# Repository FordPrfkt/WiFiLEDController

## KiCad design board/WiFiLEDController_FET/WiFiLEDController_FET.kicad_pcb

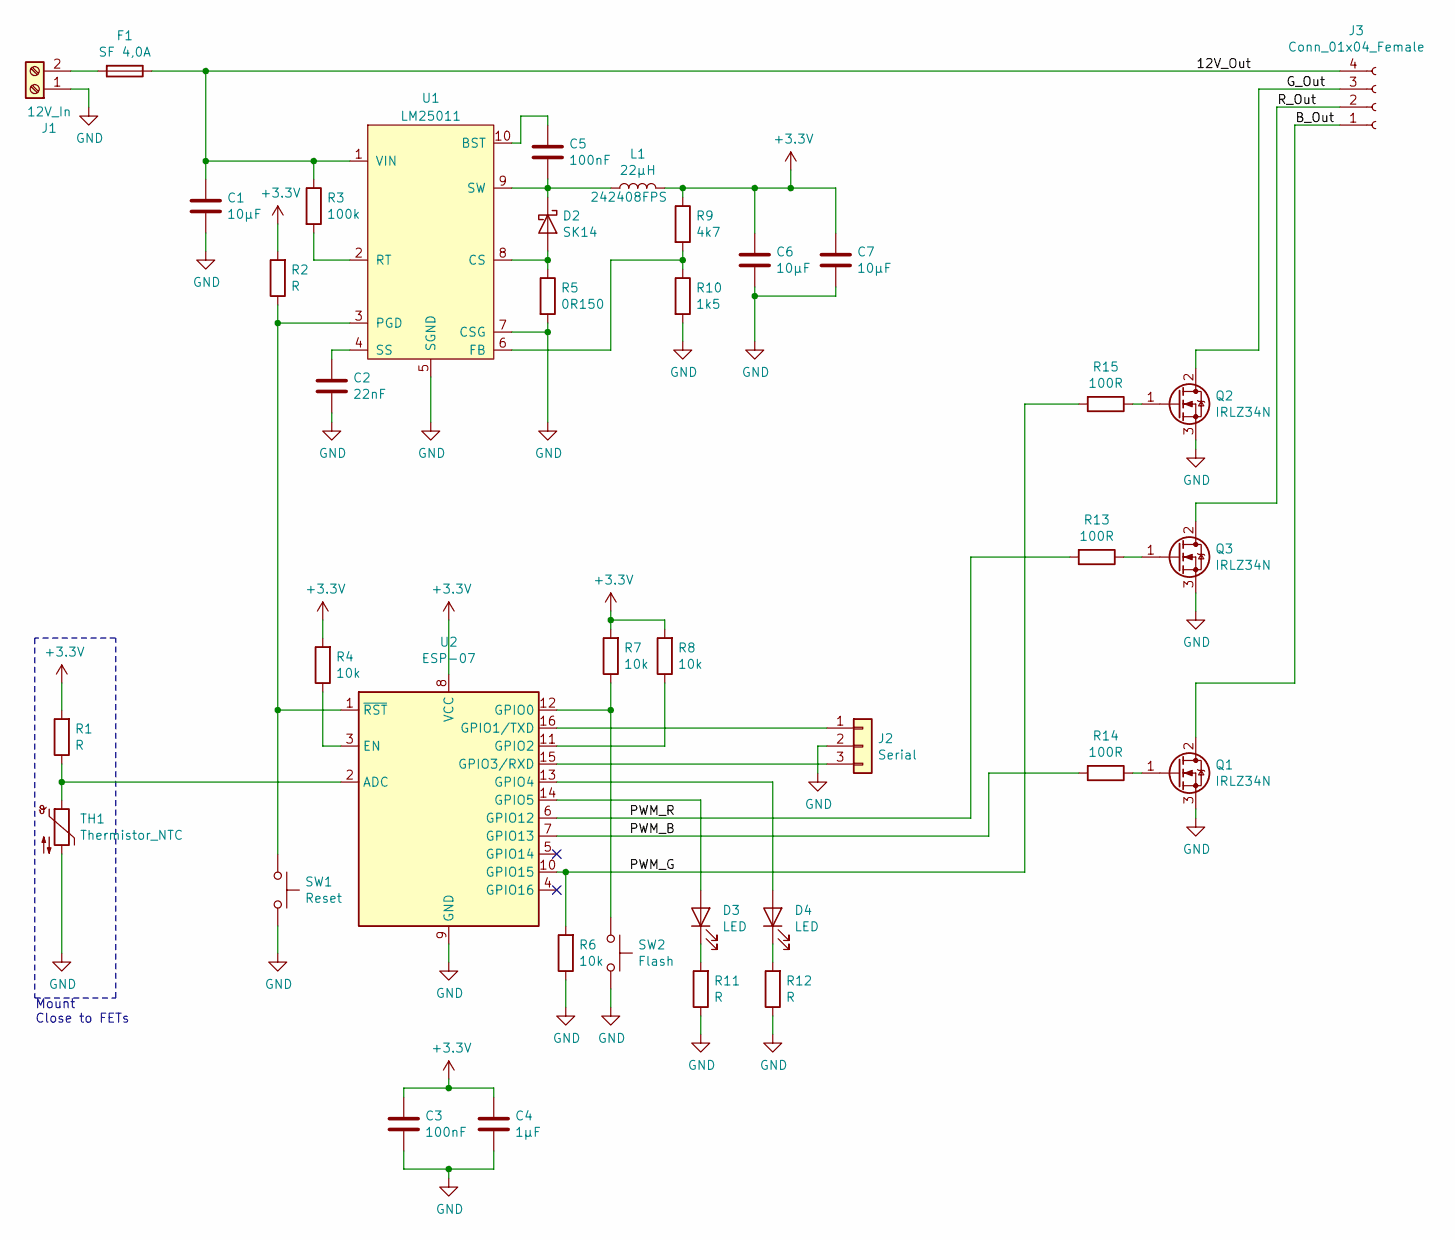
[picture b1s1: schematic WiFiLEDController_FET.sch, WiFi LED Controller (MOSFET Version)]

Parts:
C1: 10µF; C_1210_3225Metric_Pad1.42x2.65mm_HandSolder
C2: 22nF; C_0805_2012Metric_Pad1.15x1.40mm_HandSolder
C3, C5: 100nF; C_0805_2012Metric_Pad1.15x1.40mm_HandSolder
C4: 1µF; C_0805_2012Metric_Pad1.15x1.40mm_HandSolder
C6, C7: 10µF; C_1206_3216Metric_Pad1.42x1.75mm_HandSolder
D2: SK14; D_SOD-123
D3, D4: LED; LED_0805_2012Metric_Pad1.15x1.40mm_HandSolder
F1: SF 4,0A; R_Axial_DIN0207_L6.3mm_D2.5mm_P10.16mm_Horizontal
J1: 12V_In; TerminalBlock_RND_205-00001_1x02_P5.00mm_Horizontal
J2: Serial; PinHeader_1x03_P2.54mm_Vertical
J3: Conn_01x04_Female; PinSocket_1x04_P2.54mm_Horizontal
L1: 22µH; L_6.3x6.3_H3
Q1, Q2, Q3: IRLZ34N; TO-220-3_Horizontal_TabDown
R1, R2, R11, R12: R; R_0805_2012Metric_Pad1.15x1.40mm_HandSolder
R3: 100k; R_0805_2012Metric_Pad1.15x1.40mm_HandSolder
R4, R6, R7, R8: 10k; R_0805_2012Metric_Pad1.15x1.40mm_HandSolder
R5: 0R150; R_0805_2012Metric_Pad1.15x1.40mm_HandSolder
R9: 4k7; R_0805_2012Metric_Pad1.15x1.40mm_HandSolder
R10: 1k5; R_0805_2012Metric_Pad1.15x1.40mm_HandSolder
R13, R14, R15: 100R; R_0805_2012Metric_Pad1.15x1.40mm_HandSolder
SW1: Reset; SW_SPST_B3S-1000
SW2: Flash; SW_SPST_B3S-1000
TH1: Thermistor_NTC; R_0805_2012Metric_Pad1.15x1.40mm_HandSolder
U1: LM25011; HVSSOP-10
U2: ESP-07

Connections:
+3V3: C3.1, C4.1, C6.1, C7.1, L1.2, R1.2, R2.2, R4.2, R7.2, R8.2, R9.1, U2.8 (VCC)
/12V_Out: C1.1, F1.1, J3.4, R3.1, U1.1 (VIN)
/B_Out: J3.1, Q1.2 (D)
/G_Out: J3.3, Q2.2 (D)
/PWM_B: R14.2, U2.7 (GPIO13)
/PWM_G: R6.2, R15.2, U2.10 (GPIO15)
/PWM_R: R13.2, U2.6 (GPIO12)
/R_Out: J3.2, Q3.2 (D)
GND: C1.2, C2.2, C3.2, C4.2, C6.2, C7.2, J1.1, J2.2, Q1.3 (S), Q2.3 (S), Q3.3 (S), R5.2, R6.1, R10.2, R11.1, R12.1, SW1.2, SW2.2, TH1.2, U1.5 (SGND), U1.7 (CSG), U1.11 (GND), U2.9 (GND)
unnamed: C2.1, U1.4 (SS)
unnamed: C5.1, U1.10 (BST)
unnamed: C5.2, D2.1 (K), L1.1, U1.9 (SW)
unnamed: D2.2 (A), R5.1, U1.8 (CS)
unnamed: D3.1 (K), R11.2
unnamed: D3.2 (A), U2.14 (GPIO5)
unnamed: D4.1 (K), R12.2
unnamed: D4.2 (A), U2.13 (GPIO4)
unnamed: F1.2, J1.2
unnamed: J2.1, U2.16 (GPIO1/TXD)
unnamed: J2.3, U2.15 (GPIO3/RXD)
unnamed: Q1.1 (G), R14.1
unnamed: Q2.1 (G), R15.1
unnamed: Q3.1 (G), R13.1
unnamed: R1.1, TH1.1, U2.2 (ADC)
unnamed: R2.1, SW1.1, U1.3 (PGD), U2.1 (~RST)
unnamed: R3.2, U1.2 (RT)
unnamed: R4.1, U2.3 (EN)
unnamed: R7.1, SW2.1, U2.12 (GPIO0)
unnamed: R8.1, U2.11 (GPIO2)
unnamed: R9.2, R10.1, U1.6 (FB)

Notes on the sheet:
Mount Close to FETs

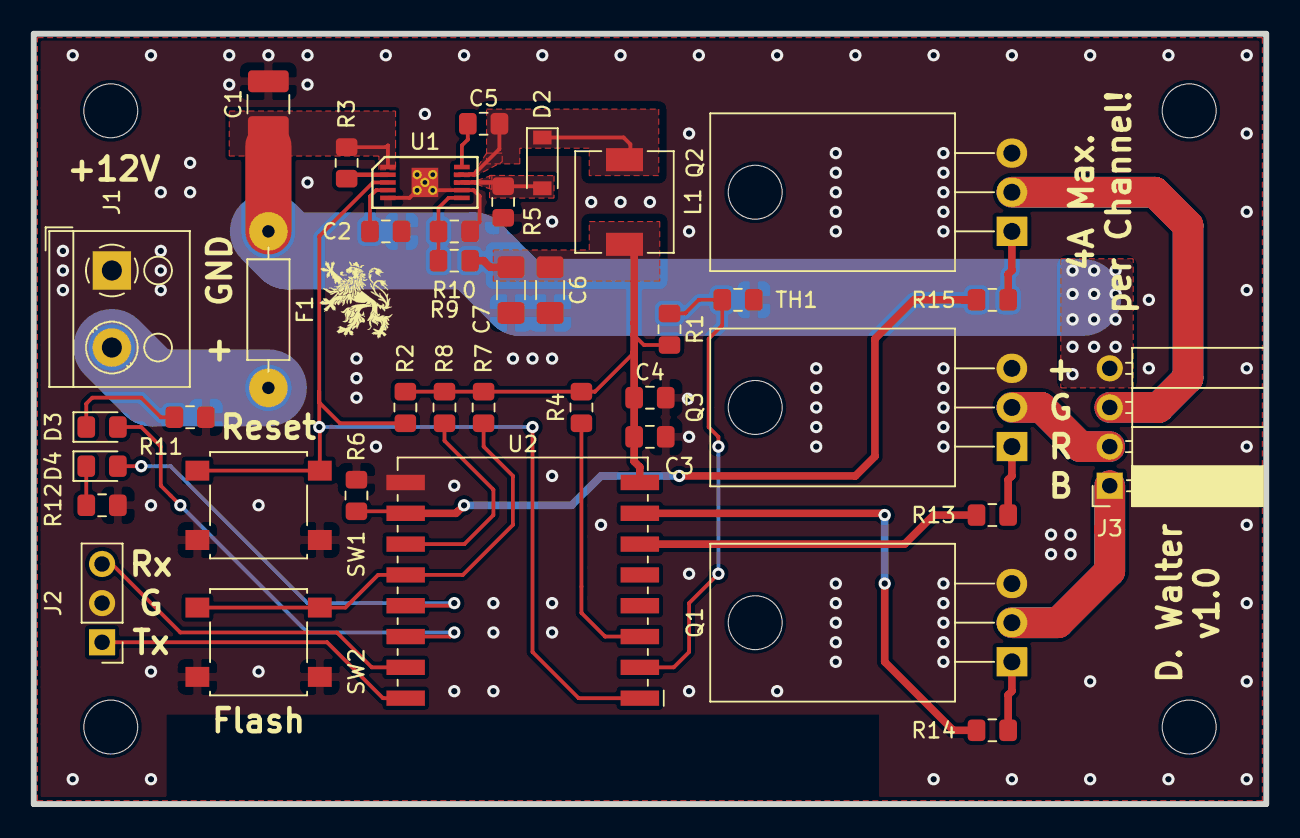
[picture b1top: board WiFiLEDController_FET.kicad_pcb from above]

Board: 2 copper layers, 80.0 x 50.0 mm, 38 parts (0 on the bottom side), 30 nets.

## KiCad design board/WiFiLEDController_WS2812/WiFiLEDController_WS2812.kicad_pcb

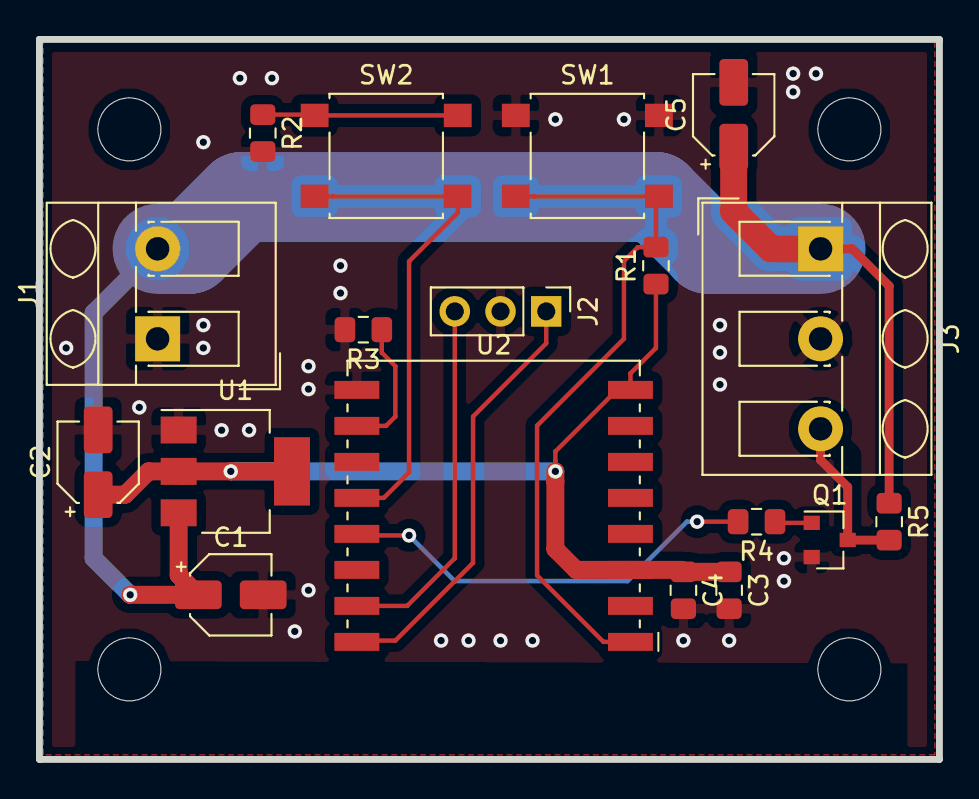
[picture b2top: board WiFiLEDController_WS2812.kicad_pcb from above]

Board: 2 copper layers, 50.0 x 40.0 mm, 18 parts (0 on the bottom side), 12 nets.

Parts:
C1, C2, C5: 10µF; CP_Elec_4x3.9
C3: 1µF; C_0805_2012Metric_Pad1.15x1.40mm_HandSolder
C4: 100nF; C_0805_2012Metric_Pad1.15x1.40mm_HandSolder
J1: Supply; TerminalBlock_RND_205-00056_1x02_P5.00mm_45Degree
J2: Serial; PinHeader_1x03_P2.54mm_Vertical
J3: LED_Strip; TerminalBlock_RND_205-00057_1x03_P5.00mm_45Degree
Q1: BC817; SOT-23
R1, R4, R5: 10k; R_0805_2012Metric_Pad1.15x1.40mm_HandSolder
R2, R3: 4k7; R_0805_2012Metric_Pad1.15x1.40mm_HandSolder
SW1: SW_Reset; SW_SPST_B3S-1000
SW2: SW_Flash; SW_SPST_B3S-1000
U1: LM1117-3.3; SOT-223-3_TabPin2
U2: ESP-07

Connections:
+3V3: C2.1, C3.1, C4.1, R1.1, U1.2, U2.3, U2.8
+5V: C1.1, C5.1, J1.2, J3.1, R5.1, U1.3
GND: C1.2, C2.2, C3.2, C4.2, C5.2, J1.1, J2.2, J3.2, Q1.2, R2.2, R3.2, SW1.1, U1.1, U2.9
unnamed: J2.1, U2.16
unnamed: J2.3, U2.15
unnamed: J3.3, Q1.3, R5.2
unnamed: Q1.1, R4.1
unnamed: R1.2, SW1.2, U2.1
unnamed: R2.1, SW2.1
unnamed: R3.1, U2.10
unnamed: R4.2, U2.13
unnamed: SW2.2, U2.12

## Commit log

2019-04-08 Layout done
2019-04-24 Minor Layout Changes
2019-07-30 Code Work in progress
